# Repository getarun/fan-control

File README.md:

Fan Control
===========

Software to control fans depending on the dew points inside and outside of the building with help of a raspberry Pi, two DHT22's, an Adafruit LCD and a relais board.

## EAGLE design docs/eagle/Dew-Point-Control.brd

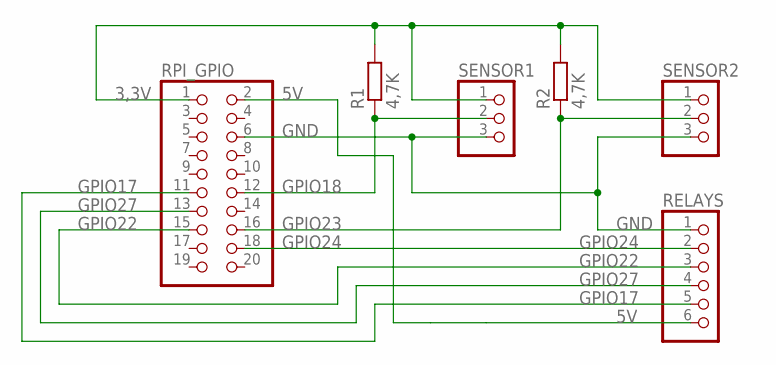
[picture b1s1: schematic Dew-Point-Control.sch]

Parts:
R1, R2: 4,7K; 0207/10
RELAYS: PINHD-1X6; 1X06
RPI_GPIO: PINHD-2X10; 2X10
SENSOR1, SENSOR2: PINHD-1X3; 1X03

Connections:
3,3V: R1.2, R2.2, RPI_GPIO.1, SENSOR1.1, SENSOR2.1
5V: RELAYS.6, RPI_GPIO.2
GND: RELAYS.1, RPI_GPIO.6, SENSOR1.3, SENSOR2.3
GPIO17: RELAYS.5, RPI_GPIO.11
GPIO18: R1.1, RPI_GPIO.12, SENSOR1.2
GPIO22: RELAYS.3, RPI_GPIO.15
GPIO23: R2.1, RPI_GPIO.16, SENSOR2.2
GPIO24: RELAYS.2, RPI_GPIO.18
GPIO27: RELAYS.4, RPI_GPIO.13

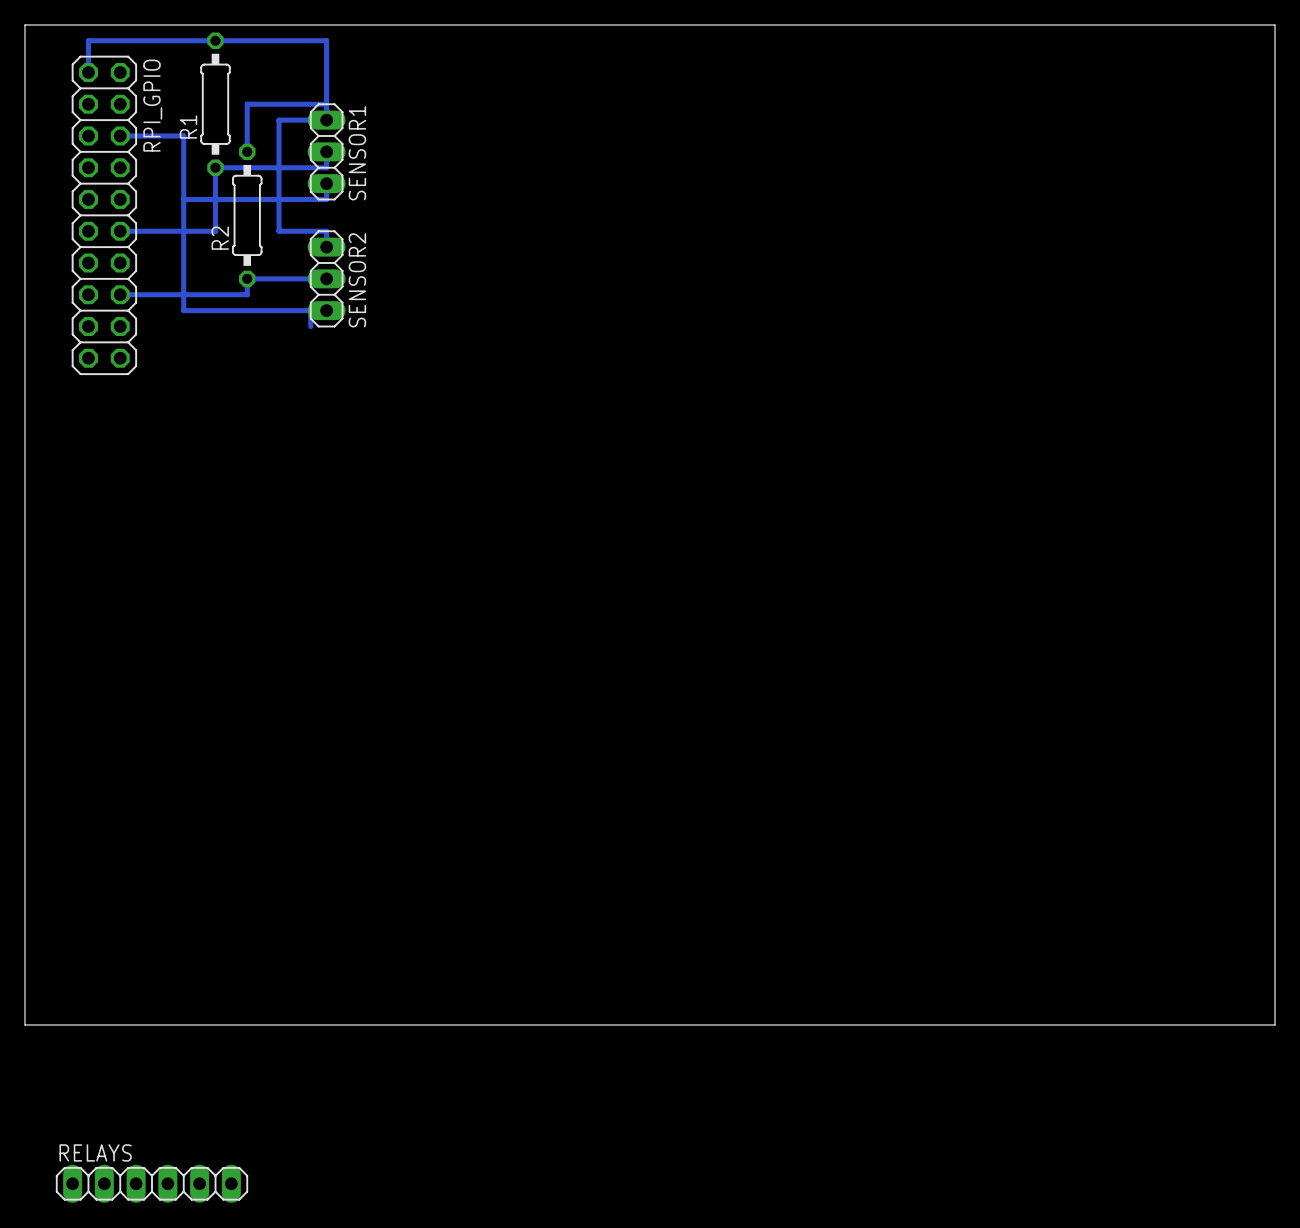
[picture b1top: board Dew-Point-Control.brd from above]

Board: 2 copper layers, 100.0 x 80.0 mm, 6 parts (0 on the bottom side), 9 nets.

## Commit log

2014-10-19 - use DHT22 to retrieve temperature and humidity - calc dew point - show data on Adafruit 16x2 LCD
2014-10-19 add schmea and board layout
2014-10-19 remove iml file
2014-11-08 implement basic relay service
2014-11-09 test commit
2014-11-09 test commit over
2014-11-09 simple display provider
2014-11-09 simple abstraction to control relays
2014-11-09 updated eagle board and schematic
2014-11-09 ignore idea and eagle temp files
2014-11-09 remove eagle temp files
2014-11-09 use introduced weather service
2014-11-09 set setup.py executable
2014-11-09 add shebang
2014-11-09 remove ez setup
2014-11-09 fix recursion error
2014-11-09 rename project and add init script
2014-11-09 fix dependencies
2014-11-09 make init script executable
2014-11-10 rename to FanControl
2014-11-11 save state
2014-11-11 update fan-control every minute
2014-11-11 fix init script
2014-11-11 set logging to info
2014-11-11 implement data log
2014-11-11 initialize state array correctly
2014-11-11 remove stateful relay service use GPIO instead
2014-11-11 reverse pin array
2014-11-11 only update fans every 30 minutes
2014-11-11 reraise initialization exception
2014-11-11 add simple website
2014-11-11 add graph library
2014-11-12 add LSB tags
2014-11-12 add dew_point to logging
2014-11-12 add simple chart for last measurements
2014-11-12 substitute chart library
2014-11-12 add new yAxis
2014-11-20 update data
2014-11-20 use google chart api
2014-11-21 create more compact degree celcius sign
2014-11-21 show and log outside weather data
2014-11-21 implement dew_point switching
2014-11-22 switch on auto control
2014-11-22 remove old chart library
2014-11-22 improve data logging logic
